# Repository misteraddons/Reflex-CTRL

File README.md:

# General
A series of drop in replacement circuit boards to convert console controllers directly to USB. Reflex CTRL uses [GP2040-CE](https://gp2040-ce.info/#/) firmware, and boasts an incredibly low 0.8ms latency.

## Controllers

### Config
`Web Config` mode = Start + Plug in USB, then visit [192.168.7.1](192.168.7.1)

### CTRL NES

Update Firmware: Select + Start + Up + Plug in USB
| Mode | Button Combo |
| --- | --- |
| Nintendo Switch Mode | B + Plug in USB |
| Xinput | A + Plug in USB |

| Shortcut | Button Combo |
| --- | --- |
| D-pad mode | Select + Start + Down |
| Left analog stick mode | Select + Start + Left |
| Right analog stick mode | Select + Start + Right |
| Home | Select + Start + Up |

### CTRL SNES

Update Firmware: Select + Start + Up + Plug in USB
| Mode | Button Combo |
| --- | --- |
| Nintendo Switch Mode | B + Plug in USB |
| Xinput | A + Plug in USB |
| DirectInput / PS3 | Y + Plug in USB |
| PS4 | X + Plug in USB* |
* PS4 mode requires additional steps. Enter `Web Config` mode, then go to `Settings` >  `Input Mode Settings` > `PS4` > `Authentication Mode Settings` for more info.

| Shortcut | Button Combo |
| --- | --- |
| D-pad mode | Select + Start + Down |
| Left analog stick mode | Select + Start + Left |
| Right analog stick mode | Select + Start + Right |
| Home | Select + Start + Up |
| Turbo enable/disable | Left + Select + Button |
| Turbo rate increase | Left + Up + Select |
| Turbo rate decrease | Left + Down + Select |

### CTRL Virtual Boy

Update Firmware: Select + Start + Up + Plug in USB
| Mode | Button Combo |
| --- | --- |
| Nintendo Switch Mode | Right DPad Down + Plug in USB |
| Xinput | Right DPad Right + Plug in USB |
| DirectInput / PS3 | Right DPad Left + Plug in USB |
| PS4 | Right DPad Up + Plug in USB* |
| Keyboard | R + Plug in USB* |
* PS4 mode requires additional steps. Enter `Web Config` mode, then go to `Settings` >  `Input Mode Settings` > `PS4` > `Authentication Mode Settings` for more info.

| Shortcut | Button Combo |
| --- | --- |
| D-pad mode | Select + Start + Down |
| Left analog stick mode | Select + Start + Left |
| Right analog stick mode | Select + Start + Right |
| Home | Select + Start + Up |

### CTRL Genesis 6

Update Firmware: Mode + Start + Up + Plug in USB
| Mode | Button Combo |
| --- | --- |
| Nintendo Switch Mode | A + Plug in USB |
| Xinput | B + Plug in USB |
| DirectInput / PS3 | X + Plug in USB |
| PS4 | Y + Plug in USB* |
* PS4 mode requires additional steps. Enter `Web Config` mode, then go to `Settings` >  `Input Mode Settings` > `PS4` > `Authentication Mode Settings` for more info.

| Shortcut | Button Combo |
| --- | --- |
| D-pad mode | Mode + Start + Down |
| Left analog stick mode | Mode + Start + Left |
| Right analog stick mode | Mode + Start + Right |
| Home | Mode + Start + Up |

### CTRL Saturn

Update Firmware: Start + Plug in USB to enter `Web Config`. Navigate to 192.168.7.1. Click `Reboot`, then `USB (BOOT SEL)`.
| Mode | Button Combo |
| --- | --- |
| Nintendo Switch Mode | A + Plug in USB |
| Xinput | B + Plug in USB |
| DirectInput / PS3 | X + Plug in USB |
| PS5 | Y + Plug in USB (Requires authentication dongle) |
* PS4 mode requires additional steps. Enter `Web Config` mode, then go to `Settings` >  `Input Mode Settings` > `PS4` > `Authentication Mode Settings` for more info.
* Xbox authentication requires an authentication dongle (TBD)

| Shortcut | Button Combo |
| --- | --- |
| D-pad mode | L + Start + Down |
| Left analog stick mode | L + Start + Left |
| Right analog stick mode | L + Start + Right |
| Home | L + Start + Up |

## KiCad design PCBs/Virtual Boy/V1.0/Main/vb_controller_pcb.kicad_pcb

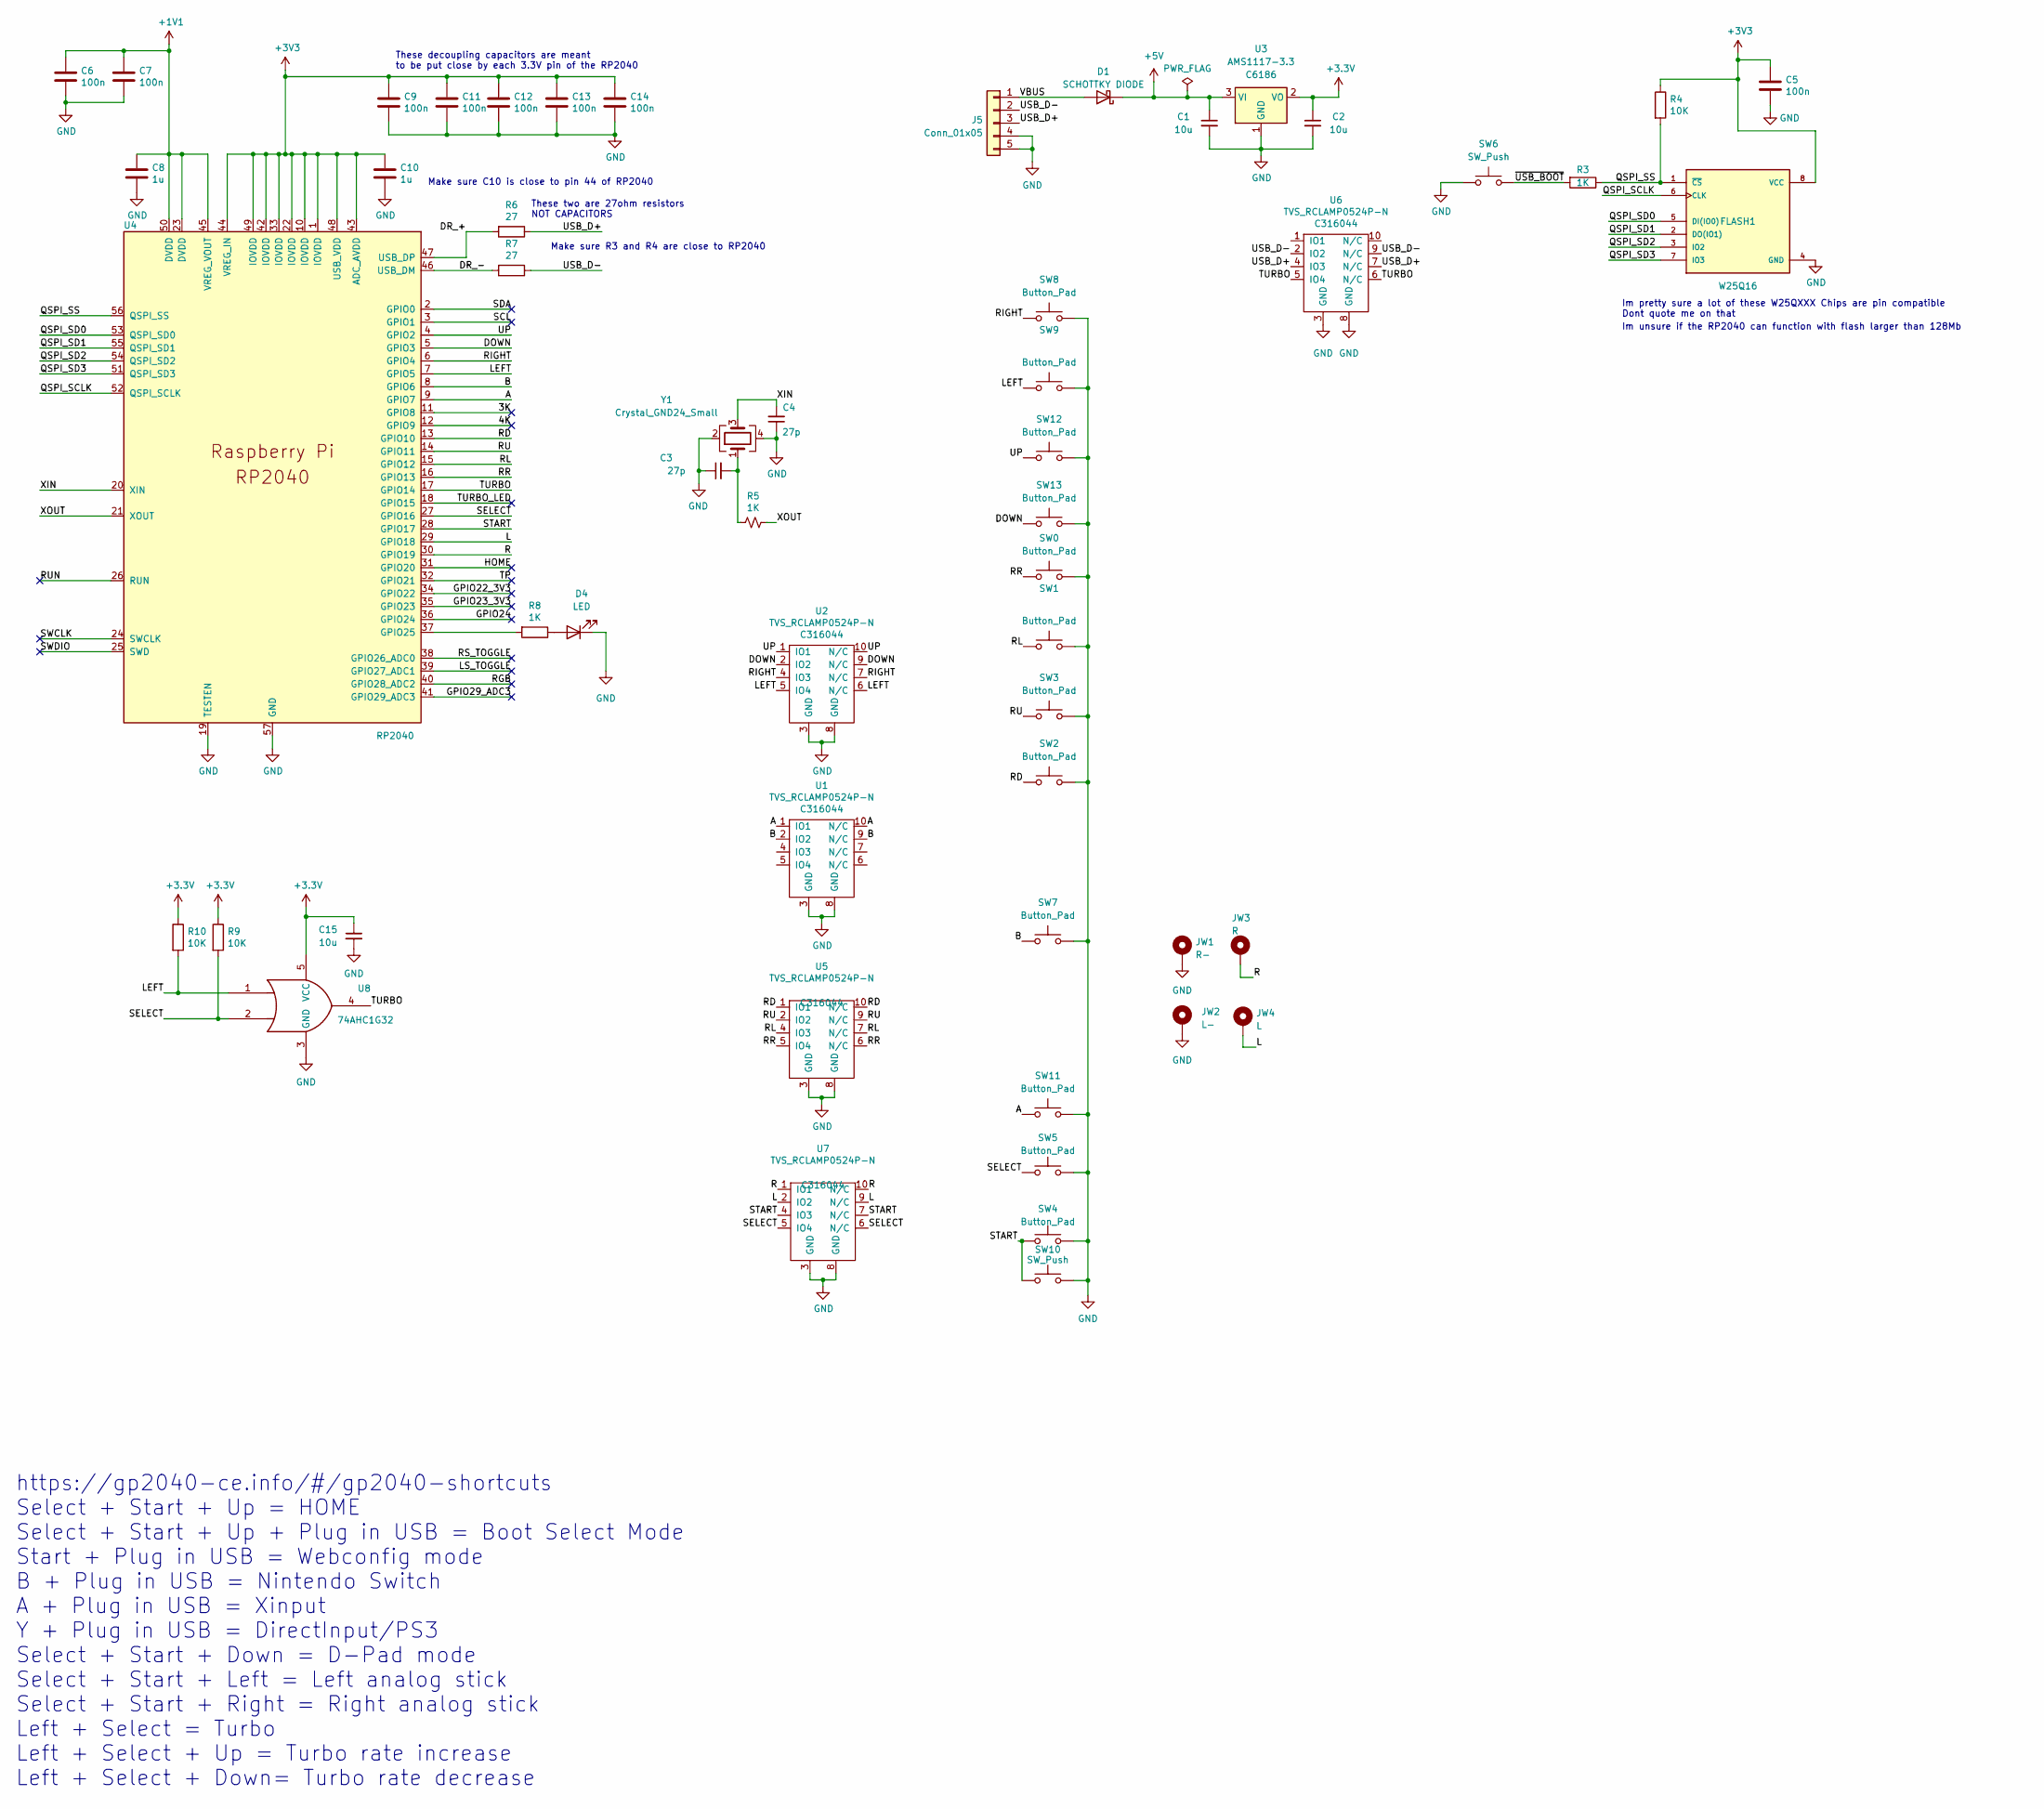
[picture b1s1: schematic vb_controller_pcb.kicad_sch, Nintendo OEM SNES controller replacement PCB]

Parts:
C1, C2, C15: 10u; C_0402_1005Metric; LCSC Part C15525
C3, C4: 27p; C_0402_1005Metric; LCSC Part C1557
C5, C6, C7, C9, C11, C12, C13, C14: 100n; C_0402_1005Metric; LCSC Part C1525
C8, C10: 1u; C_0402_1005Metric; LCSC Part C52923
D1: SCHOTTKY DIODE; D_0603_1608Metric; LCSC Part C143772
D4: LED; LED_0603_1608Metric; LCSC Part C2290
FLASH1: W25Q16; RPI_SPI_Flash_Universal_W25Q16; LCSC Part C82317
J5: Conn_01x05; JST_PH_S5B-PH-K_1x05_P2.00mm_Horizontal; LCSC Part C10402
JW1: R-; MountingHole_1.2mm_Pad
JW2: L-; MountingHole_1.2mm_Pad
JW3: R; MountingHole_1.2mm_Pad
JW4: L; MountingHole_1.2mm_Pad
R3, R5, R8: 1K; R_0402_1005Metric; LCSC Part C11702
R4, R9, R10: 10K; R_0402_1005Metric; LCSC Part C25744
R6, R7: 27; R_0402_1005Metric; LCSC Part C25100
SW0, SW1, SW2, SW3, SW8, SW9, SW12, SW13: Button_Pad; BTN_Controller_Dpad_0.3_0.3
SW4, SW5, SW7, SW11: Button_Pad; BTN_Controller_5mm_0.3_0.3
SW6, SW10: SW_Push; SW_SPST_SKQG_WithStem; LCSC Part C318884
U1, U2, U5, U6, U7: TVS_RCLAMP0524P-N; UDFN-10_1.35x2.6mm_P0.5mm; LCSC Part C316044
U3: AMS1117-3.3; SOT-223-3_TabPin2; LCSC Part C6186
U4: RP2040; RP2040-QFN-56; LCSC Part C2040
U8: 74AHC1G32; SOT-353_SC-70-5; LCSC Part C12489
Y1: Crystal_GND24_Small; Crystal_SMD_SeikoEpson_TSX3225-4Pin_3.2x2.5mm; LCSC Part C9002

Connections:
+1V1: C6.1, C7.1, C8.1, U4.23 (DVDD), U4.45 (VREG_VOUT), U4.50 (DVDD)
+5V: C1.1, D1.1 (K), U3.3 (VI)
/3K: U4.11 (GPIO8)
/4K: U4.12 (GPIO9)
/A: SW11.2, U1.1 (IO1), U1.10 (N/C), U4.9 (GPIO7)
/B: SW7.2, U1.2 (IO2), U1.9 (N/C), U4.8 (GPIO6); also elsewhere on the board
/DOWN: SW13.1, U2.2 (IO2), U2.9 (N/C), U4.5 (GPIO3)
/DR_+: R6.2, U4.47 (USB_DP)
/DR_-: R7.2, U4.46 (USB_DM)
/GPIO22_3V3: U4.34 (GPIO22)
/GPIO23_3V3: U4.35 (GPIO23)
/GPIO24: U4.36 (GPIO24)
/GPIO29_ADC3: U4.41 (GPIO29_ADC3)
/HOME: U4.31 (GPIO20)
/L: JW4.1, U4.29 (GPIO18), U7.2 (IO2), U7.9 (N/C)
/LEFT: R10.2, SW9.1, U2.5 (IO4), U2.6 (N/C), U4.7 (GPIO5), U8.1
/LS_TOGGLE: U4.39 (GPIO27_ADC1)
/QSPI_SCLK: FLASH1.6 (CLK), U4.52 (QSPI_SCLK)
/QSPI_SD0: FLASH1.5 (DI(IO0)), U4.53 (QSPI_SD0)
/QSPI_SD1: FLASH1.2 (DO(IO1)), U4.55 (QSPI_SD1)
/QSPI_SD2: FLASH1.3 (IO2), U4.54 (QSPI_SD2)
/QSPI_SD3: FLASH1.7 (IO3), U4.51 (QSPI_SD3)
/QSPI_SS: FLASH1.1 (~CS), R3.1, R4.2, U4.56 (QSPI_SS)
/R: JW3.1, U4.30 (GPIO19), U7.1 (IO1), U7.10 (N/C)
/RD: SW2.1, U4.13 (GPIO10), U5.1 (IO1), U5.10 (N/C)
/RGB: U4.40 (GPIO28_ADC2)
/RIGHT: SW8.1, U2.4 (IO3), U2.7 (N/C), U4.6 (GPIO4)
/RL: SW1.1, U4.15 (GPIO12), U5.4 (IO3), U5.7 (N/C)
/RR: SW0.1, U4.16 (GPIO13), U5.5 (IO4), U5.6 (N/C)
/RS_TOGGLE: U4.38 (GPIO26_ADC0)
/RU: SW3.1, U4.14 (GPIO11), U5.2 (IO2), U5.9 (N/C)
/RUN: U4.26 (RUN)
/SCL: U4.3 (GPIO1)
/SDA: U4.2 (GPIO0)
/SELECT: R9.2, SW5.2, U4.27 (GPIO16), U7.5 (IO4), U7.6 (N/C), U8.2
/START: SW4.2, SW10.1, U4.28 (GPIO17), U7.4 (IO3), U7.7 (N/C)
/SWCLK: U4.24 (SWCLK)
/SWDIO: U4.25 (SWD)
/TP: U4.32 (GPIO21)
/TURBO: U4.17 (GPIO14), U6.5 (IO4), U6.6 (N/C), U8.4
/TURBO_LED: U4.18 (GPIO15)
/UP: SW12.1, U2.1 (IO1), U2.10 (N/C), U4.4 (GPIO2)
/USB_D+: J5.3, R6.1, U6.4 (IO3), U6.7 (N/C)
/USB_D-: J5.2, R7.1, U6.2 (IO2), U6.9 (N/C)
/VBUS: D1.2 (A), J5.1
/XIN: C4.2, U4.20 (XIN), Y1.3
/XOUT: R5.1, U4.21 (XOUT)
/~USB_BOOT: R3.2, SW6.2
GND: C1.2, C2.2, C3.1, C4.1, C5.2, C6.2, C7.2, C8.2, C9.2, C10.2, C11.2, C12.2, C13.2, C14.2, C15.2, FLASH1.4 (GND), J5.4, J5.5, JW1.1, JW2.1, SW0.2, SW1.2, SW2.2, SW3.2, SW4.1, SW5.1, SW6.1, SW8.2, SW9.2, SW10.2, SW11.1, SW12.2, SW13.2, U1.3 (GND), U1.8 (GND), U2.3 (GND), U2.8 (GND), U3.1 (GND), U4.19 (TESTEN), U4.57 (GND), U5.3 (GND), U5.8 (GND), U6.3 (GND), U6.8 (GND), U7.3 (GND), U7.8 (GND), U8.3 (GND), Y1.2, Y1.4; also elsewhere on the board
unnamed: C3.2, R5.2, Y1.1
unnamed 50: R8.1; also elsewhere on the board
unnamed: R8.2, U4.37 (GPIO25)

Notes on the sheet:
https://gp2040-ce.info/#/gp2040-shortcuts Select + Start + Up = HOME Select + Start + Up + Plug in USB = Boot Select Mode Start + Plug in USB = Webconfig mode B + Plug in USB = Nintendo Switch A + Plug in USB = Xinput Y + Plug in USB = DirectInput/PS3 Select + Start + Down = D-Pad mode Select + Sta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
These two are 27ohm resistors NOT CAPACITORS
Make sure R3 and R4 are close to RP2040
Im pretty sure a lot of these W25QXXX Chips are pin compatible Dont quote me on that
Im unsure if the RP2040 can function with flash larger than 128Mb
These decoupling capacitors are meant to be put close by each 3.3V pin of the RP2040
Make sure C10 is close to pin 44 of RP2040

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
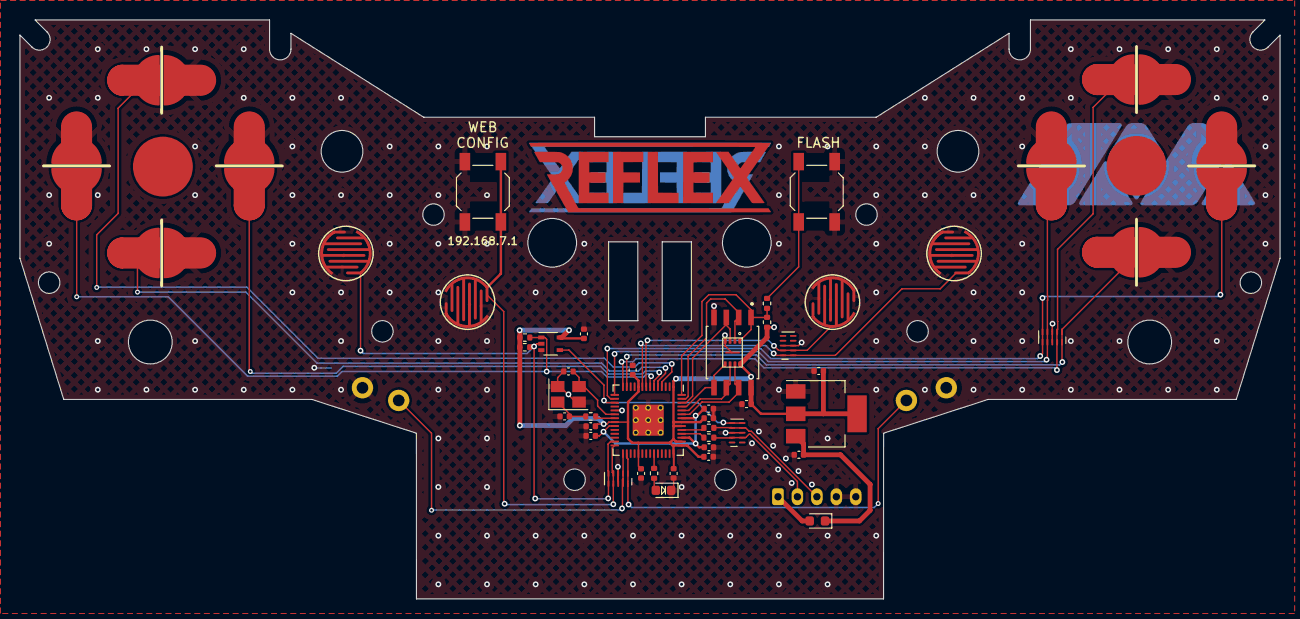
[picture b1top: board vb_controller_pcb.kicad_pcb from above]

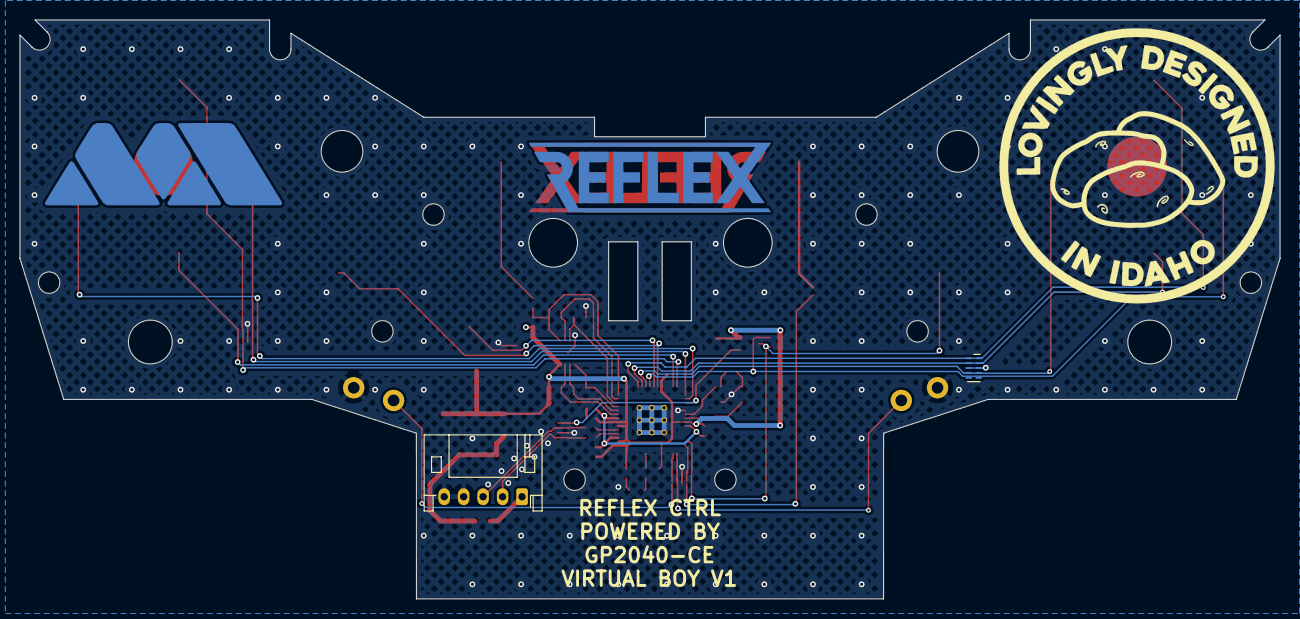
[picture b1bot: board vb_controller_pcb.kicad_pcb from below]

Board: 2 copper layers, 129.5 x 59.5 mm, 58 parts (5 on the bottom side), 36 nets.

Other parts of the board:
D2: LED; LED_0603_1608Metric
Ref**: Val**; Reflex_Copper_30mm
Ref**#2: Val**; Idaho_XL
Ref**#3: Val**; MiSTer_Addons_MA_25mm
Ref**#4: Val**; Reflex_Copper_30mm
locked: Button_Pad; BTN_Controller_5mm_0.3_0.3

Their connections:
/B: locked.2; also elsewhere on the board
GND: D2.1 (K), locked.1; also elsewhere on the board
unnamed 50: D2.2 (A); also elsewhere on the board

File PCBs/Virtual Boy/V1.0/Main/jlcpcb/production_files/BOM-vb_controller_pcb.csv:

Comment,Designator,Footprint,LCSC
Conn_01x05,J5,JST_PH_S5B-PH-K_1x05_P2.00mm_Horizontal,C10402
1K,"R3,R5,R8",R_0402_1005Metric,C11702
74AHC1G32,U8,SOT-353_SC-70-5,C12489
SCHOTTKY DIODE,D1,D_0603_1608Metric,C143772
100n,"C11,C12,C13,C14,C5,C6,C7,C9",C_0402_1005Metric,C1525
10u,"C1,C15,C2",C_0402_1005Metric,C15525
27p,"C3,C4",C_0402_1005Metric,C1557
RP2040,U4,RP2040-QFN-56,C2040
LED,D2,LED_0603_1608Metric,C2290
27,"R6,R7",R_0402_1005Metric,C25100
10K,"R10,R4,R9",R_0402_1005Metric,C25744
TVS_RCLAMP0524P-N,"U1,U2,U5,U6,U7",UDFN-10_1.35x2.6mm_P0.5mm,C316044
SW_Push,"SW10,SW6",SW_SPST_SKQG_WithStem,C318884
1u,"C10,C8",C_0402_1005Metric,C52923
AMS1117-3.3,U3,SOT-223-3_TabPin2,C6186
W25Q16,FLASH1,RPI_SPI_Flash_Universal_W25Q16,C82317
Crystal_GND24_Small,Y1,Crystal_SMD_SeikoEpson_TSX3225-4Pin_3.2x2.5mm,C9002

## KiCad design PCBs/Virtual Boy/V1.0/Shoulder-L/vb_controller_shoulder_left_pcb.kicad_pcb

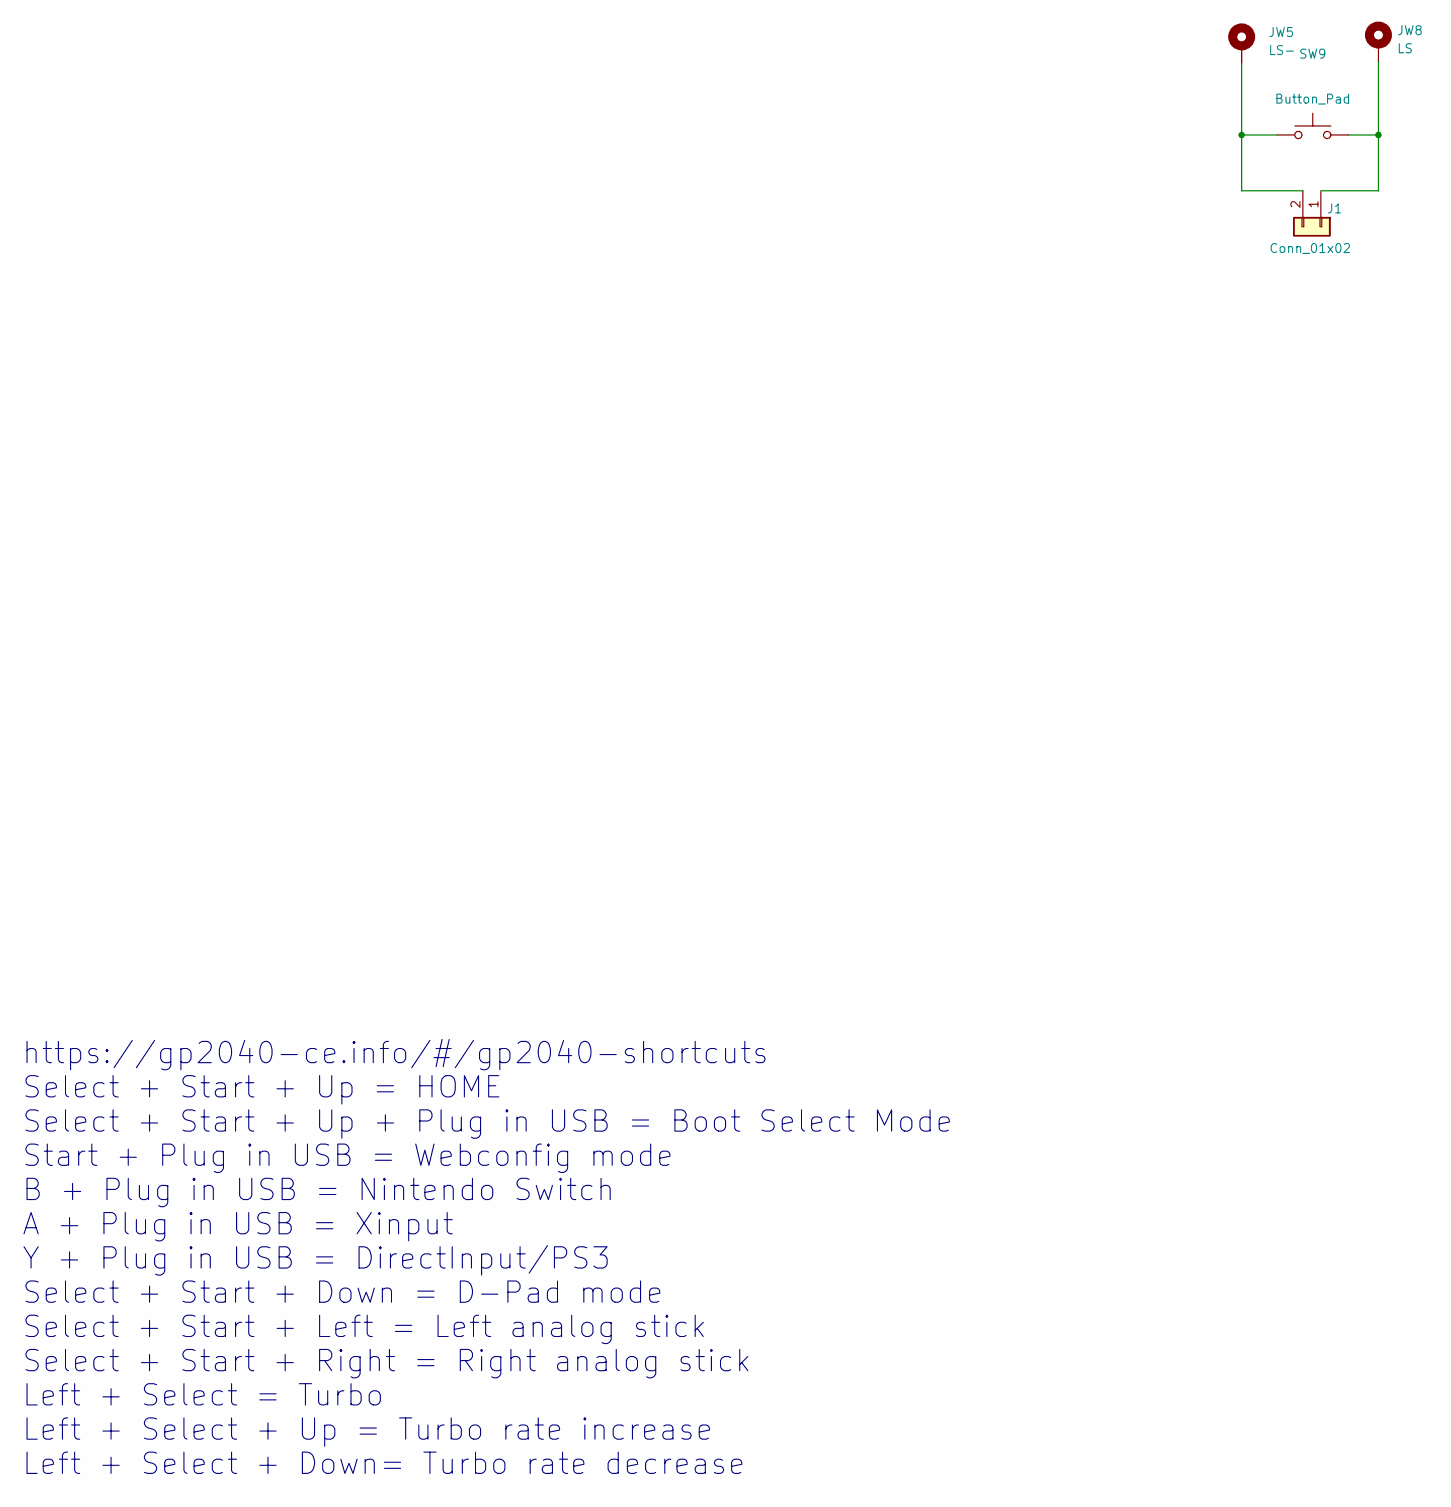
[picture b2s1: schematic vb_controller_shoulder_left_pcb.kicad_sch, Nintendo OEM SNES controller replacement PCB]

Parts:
J1: Conn_01x02; JST_PH_B2B-PH-K_1x02_P2.00mm_Vertical; LCSC Part C7433692
JW5: LS-; MountingHole_1.2mm_Pad
JW8: LS; MountingHole_1.2mm_Pad
SW9: Button_Pad; BTN_Controller_5mm_0.3_0.3

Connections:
unnamed: J1.1, JW8.1, SW9.2
unnamed: J1.2, JW5.1, SW9.1

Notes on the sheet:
https://gp2040-ce.info/#/gp2040-shortcuts Select + Start + Up = HOME Select + Start + Up + Plug in USB = Boot Select Mode Start + Plug in USB = Webconfig mode B + Plug in USB = Nintendo Switch A + Plug in USB = Xinput Y + Plug in USB = DirectInput/PS3 Select + Start + Down = D-Pad mode Select + Sta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

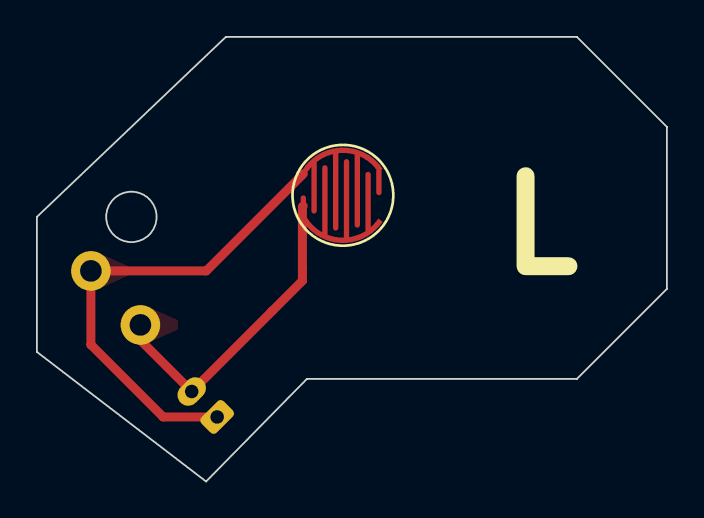
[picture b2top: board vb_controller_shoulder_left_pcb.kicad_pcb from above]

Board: 2 copper layers, 35.0 x 24.7 mm, 4 parts (1 on the bottom side), 2 nets.

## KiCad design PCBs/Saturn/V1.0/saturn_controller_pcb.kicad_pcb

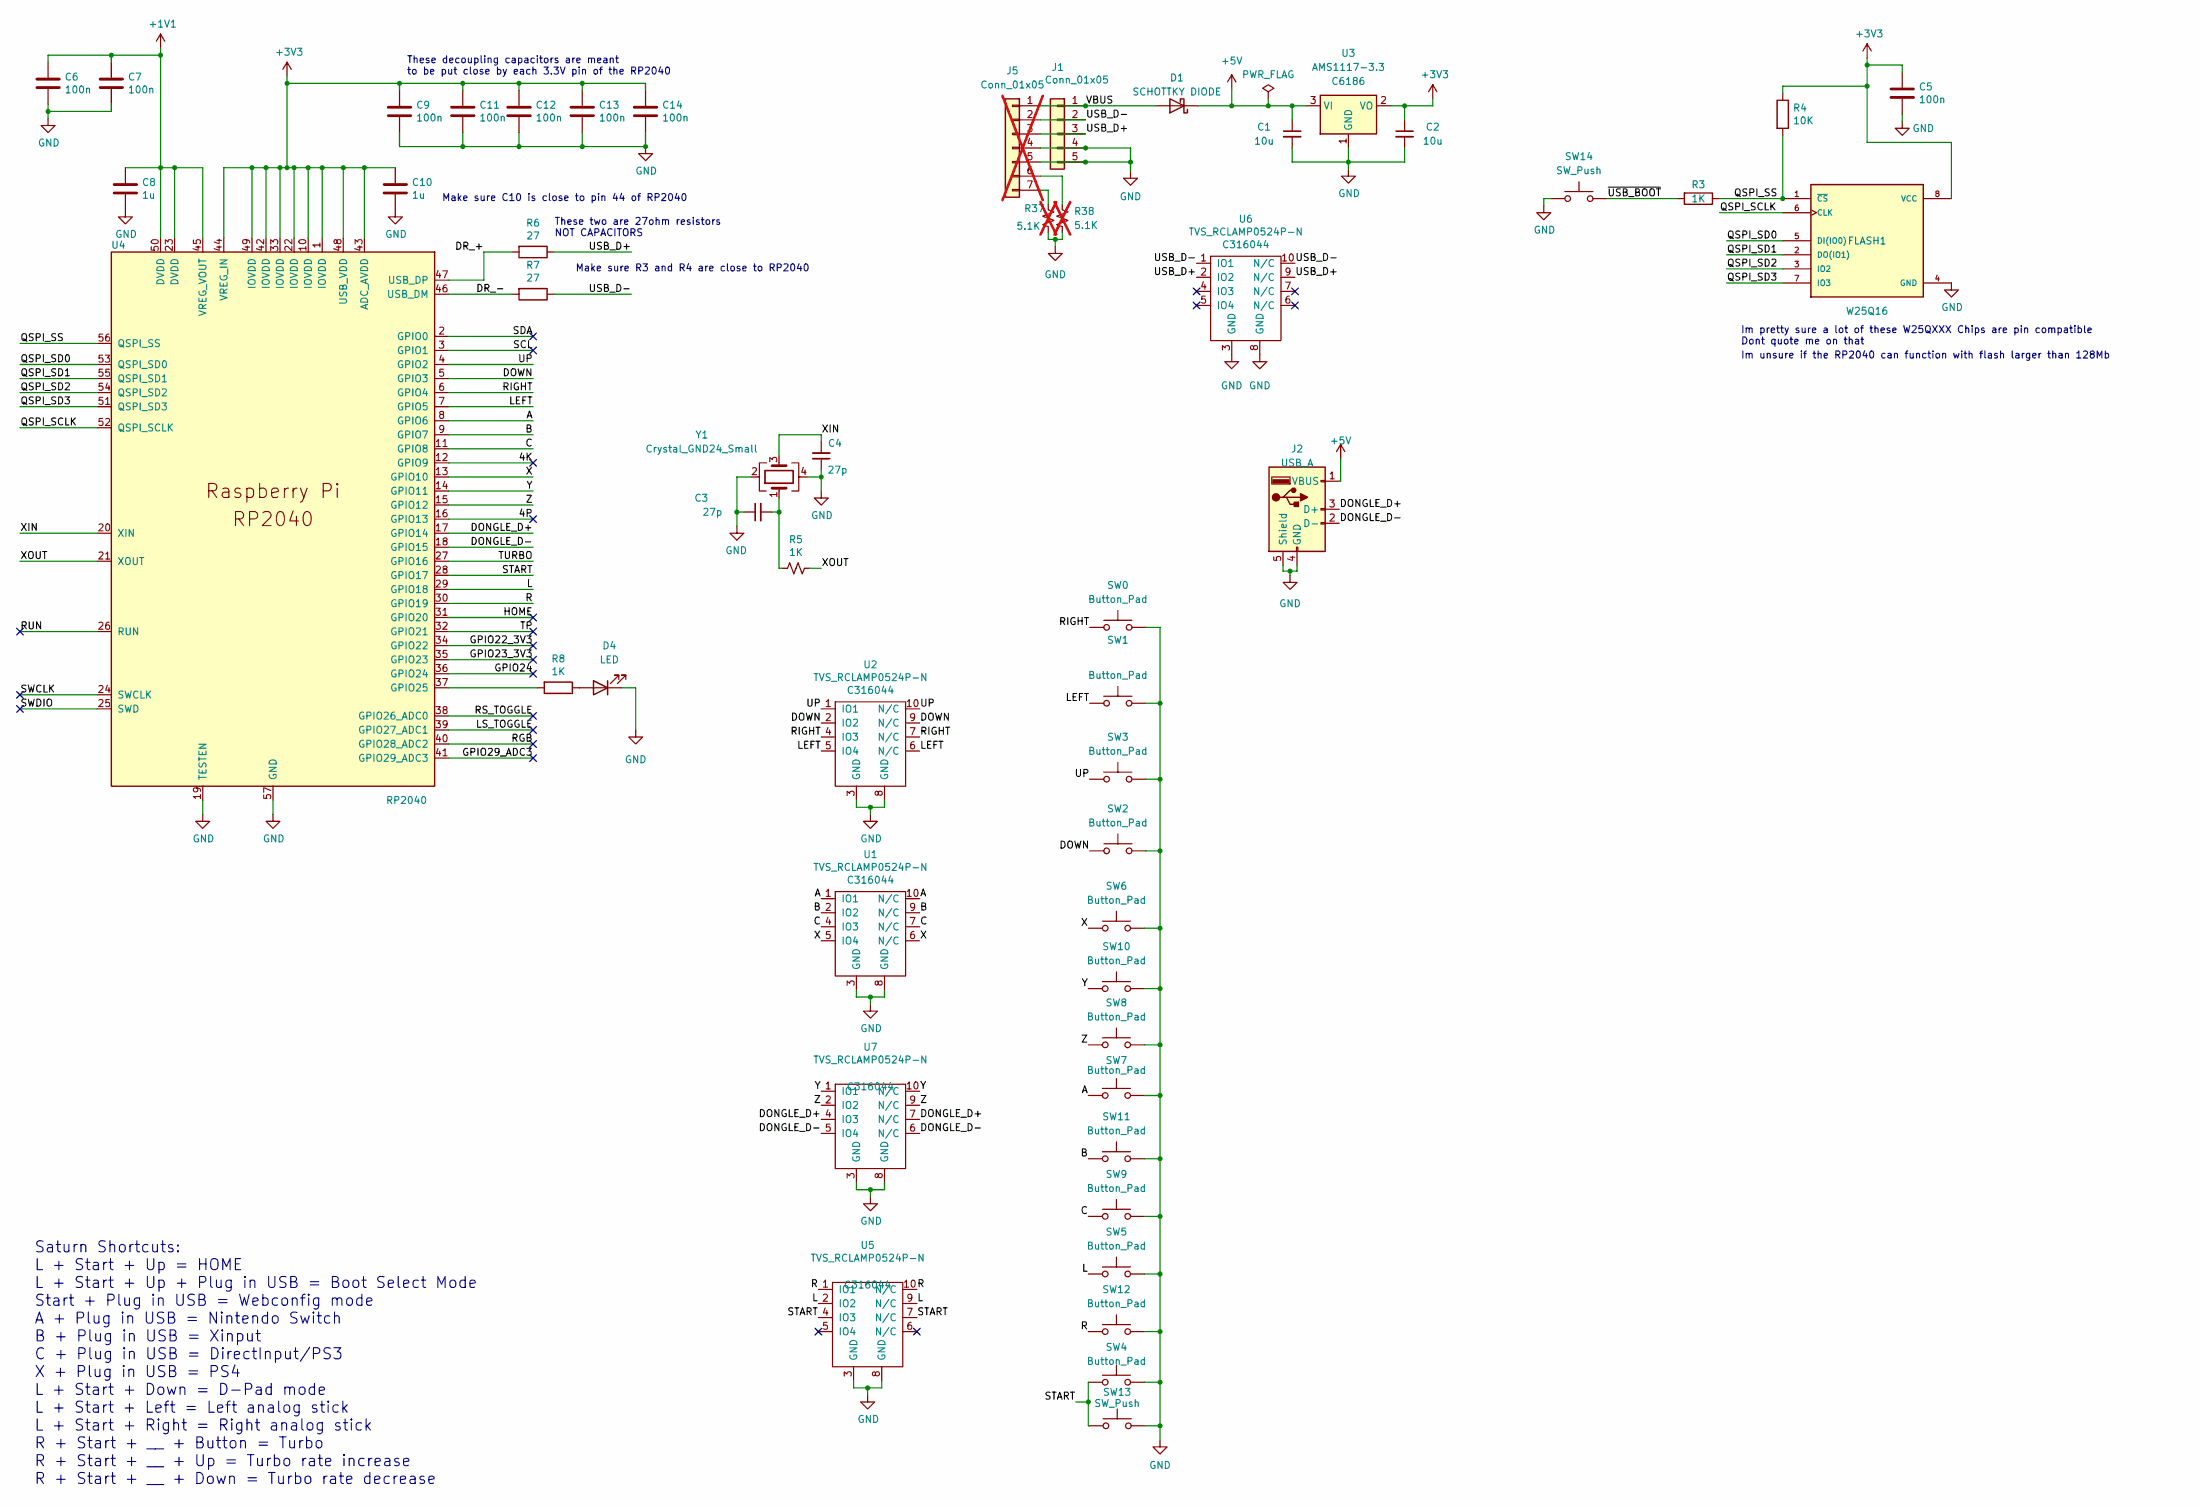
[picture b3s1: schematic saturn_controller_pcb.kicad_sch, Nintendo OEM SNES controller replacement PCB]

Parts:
C1, C2: 10u; C_0402_1005Metric; LCSC Part C15525
C3, C4: 27p; C_0402_1005Metric; LCSC Part C1557
C5, C6, C7, C9, C11, C12, C13, C14: 100n; C_0402_1005Metric; LCSC Part C1525
C8, C10: 1u; C_0402_1005Metric; LCSC Part C52923
D1: SCHOTTKY DIODE; D_0603_1608Metric; LCSC Part C143772
D4: LED; LED_0603_1608Metric; LCSC Part C2290
FLASH1: W25Q16; RPI_SPI_Flash_Universal_W25Q16; LCSC Part C2843335
J1: Conn_01x05; JST_PH_S5B-PH-K_1x05_P2.00mm_Horizontal; LCSC Part C10402
J2: USB_A; USB2_A_HOR_C2345; LCSC Part C2345
J5: Conn_01x05; JST_PH_S7B-PH-K_1x07_P2.00mm_Horizontal; LCSC Part C5342447; not fitted
R3, R5, R8: 1K; R_0402_1005Metric; LCSC Part C11702
R4: 10K; R_0402_1005Metric; LCSC Part C25744
R6, R7: 27; R_0402_1005Metric; LCSC Part C25100
R37, R38: 5.1K; R_0402_1005Metric; LCSC Part C25905; not fitted
SW0, SW1, SW2, SW3: Button_Pad; BTN_Controller_Saturn
SW4, SW6, SW7, SW8, SW9, SW10, SW11: Button_Pad; BTN_Controller_5mm_0.3_0.3
SW5, SW12: Button_Pad; SW_Tactile_SPST_Angled_PTS645Vx39-2LFS; LCSC Part C127680
SW13, SW14: SW_Push; SW_SPST_SKQG_WithStem; LCSC Part C318884
U1, U5, U6, U7: TVS_RCLAMP0524P-N; UDFN-10_1.35x2.6mm_P0.5mm; LCSC Part C316044
U2: TVS_RCLAMP0524P-N; UDFN-10_1.35x2.6mm_P0.5mm; MPN C316044; LCSC Part C316044
U3: AMS1117-3.3; SOT-223-3_TabPin2; LCSC Part C6186
U4: RP2040; RP2040-QFN-56; LCSC Part C2040
Y1: Crystal_GND24_Small; Crystal_SMD_SeikoEpson_TSX3225-4Pin_3.2x2.5mm; LCSC Part C9002

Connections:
+1V1: C6.1, C7.1, C8.1, U4.23 (DVDD), U4.45 (VREG_VOUT), U4.50 (DVDD)
+3V3: C2.1, C5.1, C9.1, C10.1, C11.1, C12.1, C13.1, C14.1, FLASH1.8 (VCC), R4.1, U3.2 (VO), U4.1 (IOVDD), U4.10 (IOVDD), U4.22 (IOVDD), U4.33 (IOVDD), U4.42 (IOVDD), U4.43 (ADC_AVDD), U4.44 (VREG_IN), U4.48 (USB_VDD), U4.49 (IOVDD)
+5V: C1.1, D1.1 (K), J2.1 (VBUS), U3.3 (VI)
/4K: U4.12 (GPIO9)
/4P: U4.16 (GPIO13)
/A: SW7.2, U1.1 (IO1), U1.10 (N/C), U4.8 (GPIO6)
/B: SW11.2, U1.2 (IO2), U1.9 (N/C), U4.9 (GPIO7)
/C: SW9.2, U1.4 (IO3), U1.7 (N/C), U4.11 (GPIO8)
/DONGLE_D+: J2.3 (D+), U4.17 (GPIO14), U7.4 (IO3), U7.7 (N/C)
/DONGLE_D-: J2.2 (D-), U4.18 (GPIO15), U7.5 (IO4), U7.6 (N/C)
/DOWN: SW2.1, U2.2 (IO2), U2.9 (N/C), U4.5 (GPIO3)
/DR_+: R6.2, U4.47 (USB_DP)
/DR_-: R7.2, U4.46 (USB_DM)
/GPIO22_3V3: U4.34 (GPIO22)
/GPIO23_3V3: U4.35 (GPIO23)
/GPIO24: U4.36 (GPIO24)
/GPIO29_ADC3: U4.41 (GPIO29_ADC3)
/HOME: U4.31 (GPIO20)
/L: SW5.2, U4.29 (GPIO18), U5.2 (IO2), U5.9 (N/C)
/LEFT: SW1.1, U2.5 (IO4), U2.6 (N/C), U4.7 (GPIO5)
/LS_TOGGLE: U4.39 (GPIO27_ADC1)
/QSPI_SCLK: FLASH1.6 (CLK), U4.52 (QSPI_SCLK)
/QSPI_SD0: FLASH1.5 (DI(IO0)), U4.53 (QSPI_SD0)
/QSPI_SD1: FLASH1.2 (DO(IO1)), U4.55 (QSPI_SD1)
/QSPI_SD2: FLASH1.3 (IO2), U4.54 (QSPI_SD2)
/QSPI_SD3: FLASH1.7 (IO3), U4.51 (QSPI_SD3)
/QSPI_SS: FLASH1.1 (~CS), R3.1, R4.2, U4.56 (QSPI_SS)
/R: SW12.2, U4.30 (GPIO19), U5.1 (IO1), U5.10 (N/C)
/RGB: U4.40 (GPIO28_ADC2)
/RIGHT: SW0.1, U2.4 (IO3), U2.7 (N/C), U4.6 (GPIO4)
/RS_TOGGLE: U4.38 (GPIO26_ADC0)
/RUN: U4.26 (RUN)
/SCL: U4.3 (GPIO1)
/SDA: U4.2 (GPIO0)
/START: SW4.2, SW13.1, U4.28 (GPIO17), U5.4 (IO3), U5.7 (N/C)
/SWCLK: U4.24 (SWCLK)
/SWDIO: U4.25 (SWD)
/TP: U4.32 (GPIO21)
/TURBO: U4.27 (GPIO16)
/UP: SW3.1, U2.1 (IO1), U2.10 (N/C), U4.4 (GPIO2)
/USB_D+: J1.3, J5.3, R6.1, U6.2 (IO2), U6.9 (N/C)
/USB_D-: J1.2, J5.2, R7.1, U6.1 (IO1), U6.10 (N/C)
/VBUS: D1.2 (A), J1.1, J5.1
/X: SW6.2, U1.5 (IO4), U1.6 (N/C), U4.13 (GPIO10)
/XIN: C4.2, U4.20 (XIN), Y1.3
/XOUT: R5.1, U4.21 (XOUT)
/Y: SW10.2, U4.14 (GPIO11), U7.1 (IO1), U7.10 (N/C)
/Z: SW8.2, U4.15 (GPIO12), U7.2 (IO2), U7.9 (N/C)
/~USB_BOOT: R3.2, SW14.2
GND: C1.2, C2.2, C3.1, C4.1, C5.2, C6.2, C7.2, C8.2, C9.2, C10.2, C11.2, C12.2, C13.2, C14.2, FLASH1.4 (GND), J1.4, J1.5, J2.4 (GND), J2.5 (Shield), SW0.2, SW1.2, SW2.2, SW3.2, SW4.1, SW5.1, SW6.1, SW7.1, SW8.1, SW9.1, SW10.1, SW11.1, SW12.1, SW13.2, SW14.1, U1.3 (GND), U1.8 (GND), U2.3 (GND), U2.8 (GND), U3.1 (GND), U4.19 (TESTEN), U4.57 (GND), U5.3 (GND), U5.8 (GND), U6.3 (GND), U6.8 (GND), U7.3 (GND), U7.8 (GND), Y1.2, Y1.4; also elsewhere on the board
unnamed: C3.2, R5.2, Y1.1
unnamed 51: R8.1; also elsewhere on the board
unnamed: J5.6, R38.2
unnamed: J5.7, R37.2
unnamed: R8.2, U4.37 (GPIO25)

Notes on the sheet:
Saturn Shortcuts: L + Start + Up = HOME L + Start + Up + Plug in USB = Boot Select Mode Start + Plug in USB = Webconfig mode A + Plug in USB = Nintendo Switch B + Plug in USB = Xinput C + Plug in USB = DirectInput/PS3 X + Plug in USB = PS4 L + Start + Down = D-Pad mode L + Start + Left = Left analo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
These two are 27ohm resistors NOT CAPACITORS
Make sure R3 and R4 are close to RP2040
Im pretty sure a lot of these W25QXXX Chips are pin compatible Dont quote me on that
Im unsure if the RP2040 can function with flash larger than 128Mb
These decoupling capacitors are meant to be put close by each 3.3V pin of the RP2040
Make sure C10 is close to pin 44 of RP2040

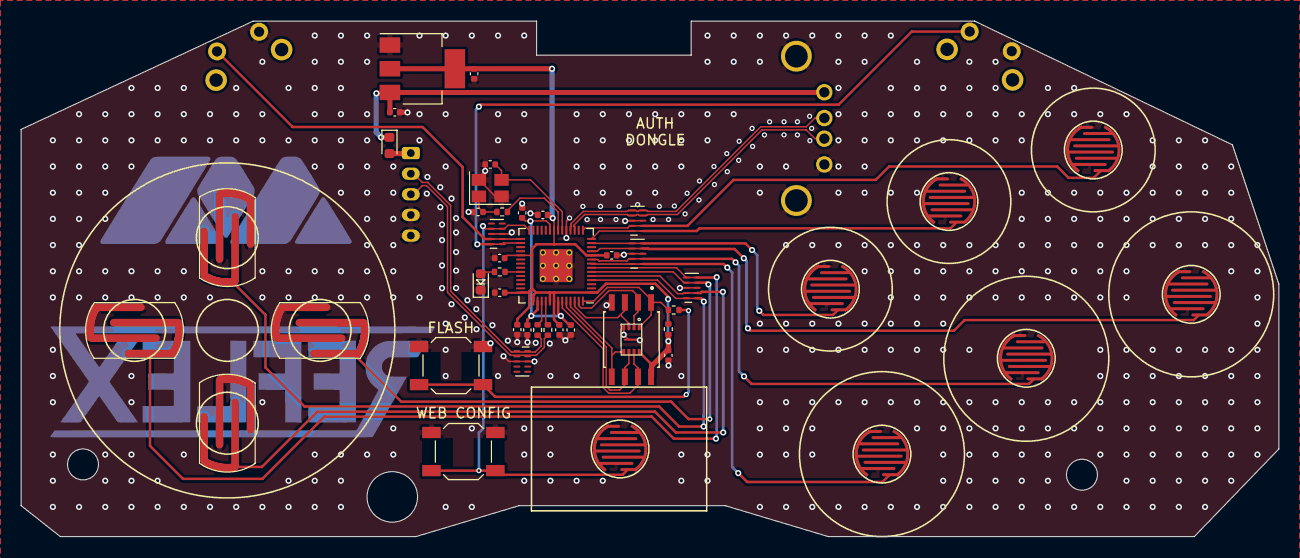
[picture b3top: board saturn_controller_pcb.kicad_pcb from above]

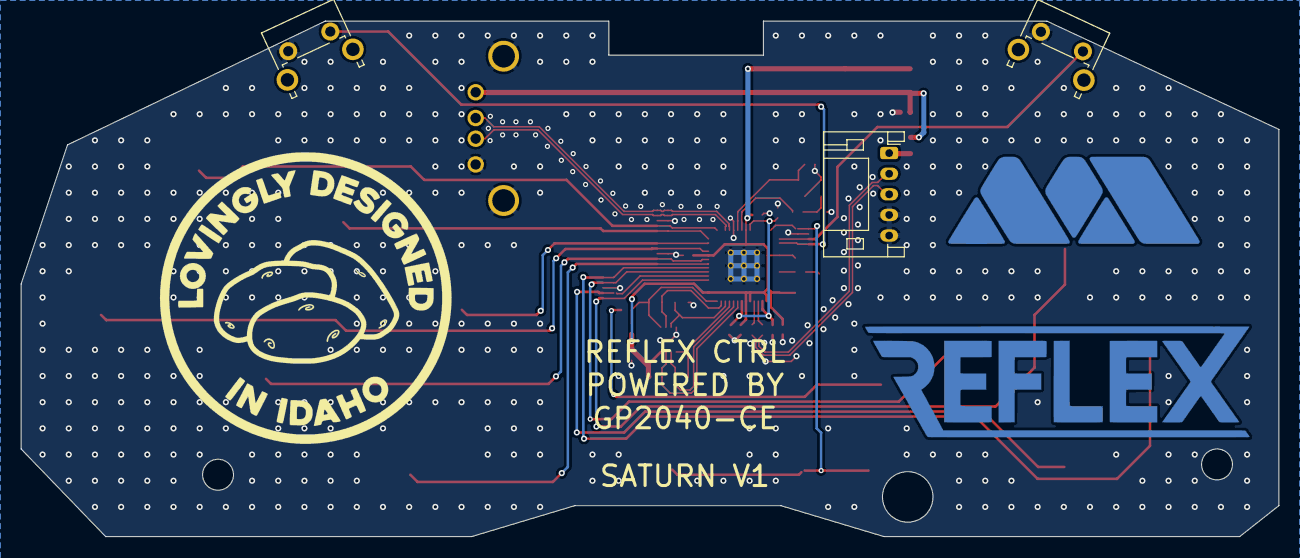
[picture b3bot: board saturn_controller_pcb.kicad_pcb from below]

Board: 2 copper layers, 122.0 x 50.0 mm, 51 parts (6 on the bottom side), 36 nets.

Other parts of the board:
D2: LED; LED_0603_1608Metric
Ref**: Val**; Idaho_XL
Ref**#2: Val**; MiSTer_Addons_MA_25mm
Ref**#3: Val**; Reflex_Copper_45mm

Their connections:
GND: D2.1 (K); also elsewhere on the board
unnamed 51: D2.2 (A); also elsewhere on the board

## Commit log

2023-08-04 SNES CTRL
2024-04-17 Update Images
2024-04-17 Shrink images
2024-04-17 Update images, add KiCad source files

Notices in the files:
PCBs/Saturn/V1.0/saturn_controller_pcb.kicad_pcb:
http://creativecommons.org/licenses/by-sa/4.0
This document describes Open Hardware and is licensed under the Creative Commons
(c) 2022 Bob Taylor
